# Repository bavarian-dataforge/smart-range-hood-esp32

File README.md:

# Smart Range Hood ESP32

**English** · [Deutsch](README.de.md)

**Open-source ESP32 controller for a GUTMANN kitchen range hood**

An open-source project to replace the unavailable original control electronics of a GUTMANN kitchen extractor hood with a custom ESP32-based controller.

The project combines embedded firmware, PCB design with KiCad, local operation and optional smart-home integration via MQTT and Home Assistant.

## Project Goals

- Replace the original range hood control board
- Control fan operation and lighting
- Provide multiple fan speed levels and a boost mode
- Support local operation without Wi-Fi
- Integrate with Home Assistant via MQTT
- Develop a documented, maintainable hardware and software solution

## Existing Hardware

| Component | Specification |
|---|---|
| Range hood | GUTMANN |
| Motor | 109942-00 |
| Supply | 230 V AC / 50 Hz |
| Rated power | 260 W |
| Rated current | 1.15 A |
| Rated speed | 2100 rpm |
| Run capacitor | 6.5 µF / 450 V AC |
| Available PCB space | 140 × 180 mm |
| EMI filter | Schurter FMW2-52-6/0.5 (5500.2044), 6 A — kept in the supply line |
| Lighting | 12 V G4 spots (to be replaced by G4 LED) |
| Controller | ESP32-WROOM-32U DevKitC V4 |

The motor has been successfully tested at full speed.

The motor is a single-phase permanent-split capacitor (PSC) motor: main winding, auxiliary winding with a 6.5 µF run capacitor, thermal cut-out. It has no speed taps.

## Speed Control

**Capacitive step speed control** (no phase-angle control — PSC motors hum and overheat on triac dimmers):

| Level | Relay | Series capacitor | Note |
|---|---|---|---|
| 3 (full) | K1 | none, direct | identical to the motor on mains |
| 2 | K4 | ~15–20 µF / 450 V AC | estimate, tune in bench test |
| 1 | K3 | ~10–12 µF / 450 V AC | estimate, tune in bench test |
| (reserve) | K2 | — | optional 4th level |

A series capacitor acts as a nearly loss-free reactance (X = 1/(2πfC)) and lowers the motor voltage. Relays are interlocked in firmware; every start from standstill runs 2 s at full speed (kick-start) before dropping to the target level.

Estimate: motor ≈ 200 Ω (230 V / 1.15 A, nearly resistive with its run capacitor); motor voltage = 230 V · R / √(R² + X_C²). The values are validated on the bench before the PCB is ordered — see [test setup](docs/images/testaufbau-kondensatoren.png).

## Planned Architecture

```text
Local User Interface
         |
         v
       ESP32 <---- Wi-Fi / MQTT
         |              |
         |        Home Assistant
         |
         v
ULN2003A relay driver          AO3400A MOSFET
         |                            |
   4 relays (Finder 40.31)      12 V LED lighting (PWM dimming)
         |
   series capacitors  ---->  Fan motor (PSC, 230 V)

Mains: fuse T 2.5 A, varistor, X2 capacitor, Mean Well IRM-20-12 (isolated 12 V)
Fallback control: Shelly BLU button (BLE, works without Wi-Fi)
```

## Repository Structure

```text
smart-range-hood-esp32/
├── README.md                 # English
├── README.de.md              # German
├── docs/
│   ├── konzept.md            # full concept, checklists, test plan (German)
│   └── images/               # nameplates, filter, hood terminal space
├── hardware/
│   ├── kicad/                # Python generators + KiCad project
│   │   ├── generate_schematic.py
│   │   ├── generate_pcb.py   # placement, net classes, design rules
│   │   ├── route_pcb.py      # own router (8 mm mains/SELV, 3 mm mains/mains)
│   │   ├── make_3d_terminals.py
│   │   └── dunstabzug-steuerplatine/
│   ├── gerber/               # fabrication output
│   ├── traegerplatte/        # carrier plate drilling template 1:1 (Python → SVG)
│   └── einkaufsliste-reichelt.md   # BOM with Reichelt links (German)
└── firmware/
    └── esphome/              # ESPHome test configurations
```

## Development Roadmap

- [x] Identify motor specifications
- [x] Verify motor operation at full speed
- [x] Confirm suitable motor speed-control method
- [x] Identify lighting supply and control requirements
- [x] Define ESP32 hardware architecture
- [x] Create KiCad schematic
- [x] Design PCB (160 × 100 mm, 2 layers, THT, DRC clean)
- [ ] Bench-test series capacitor values
- [ ] Electrical review of the mains side, then order PCB
- [ ] Implement ESP32 firmware (ESPHome test configs exist)
- [ ] Integrate MQTT and Home Assistant
- [ ] Perform electrical safety and functional testing

## Build the PCB from source

```bash
KP=/Applications/KiCad/KiCad.app/Contents/Frameworks/Python.framework/Versions/3.9/bin/python3   # KiCad's Python (macOS)
cd hardware/kicad
$KP generate_schematic.py
$KP generate_pcb.py && python3 route_pcb.py && $KP generate_pcb.py --apply-routes
```

## Electrical Safety

This project involves **230 V AC mains voltage** and a motor with a run capacitor.

The ESP32 low-voltage circuitry must be galvanically isolated from hazardous mains circuits. Appropriate protection, creepage and clearance distances, thermal design, enclosure requirements and EMC considerations must be addressed.

Motor control must not be implemented using an unverified dimmer or PWM circuit. Any mains-powered hardware requires appropriate professional review and testing before operation.

## Project Status

**PCB designed, awaiting electrical review and bench test.**

Schematic (ERC clean), routed PCB (DRC clean, 8 mm clearance/creepage mains ↔ SELV with milled slot, 3 mm mains ↔ mains) and Gerber files exist. Not yet built or tested — do not use as-is.

## License

To be determined.

---

Developed by **Bavarian Data Forge**.

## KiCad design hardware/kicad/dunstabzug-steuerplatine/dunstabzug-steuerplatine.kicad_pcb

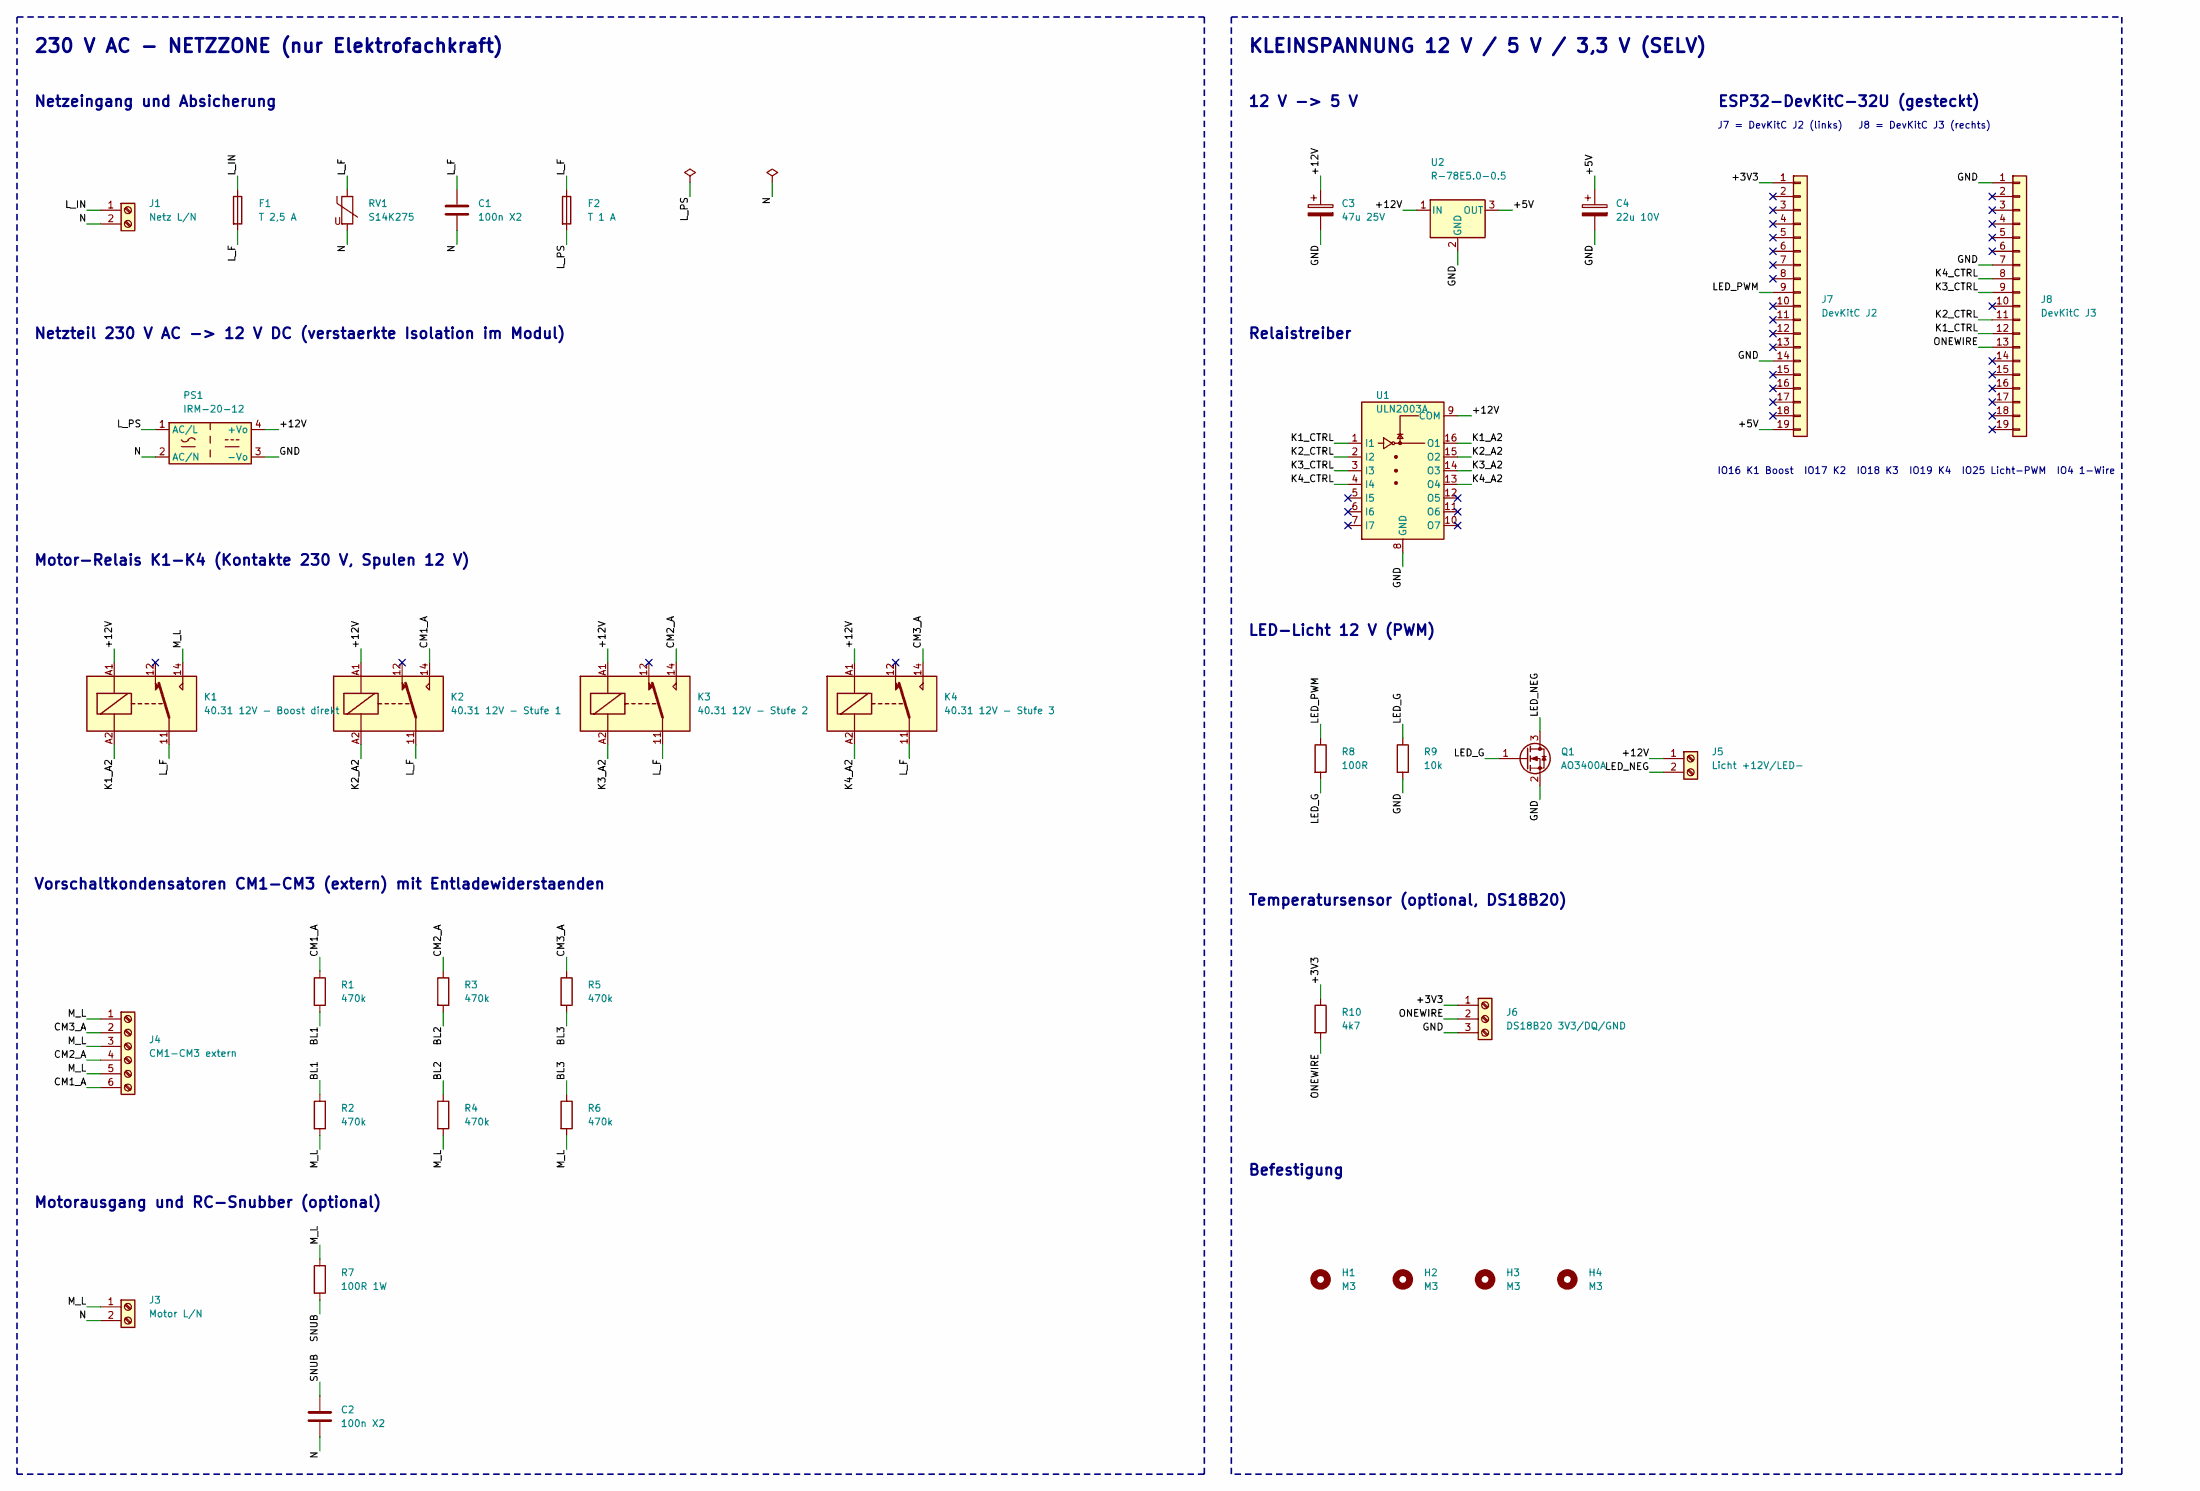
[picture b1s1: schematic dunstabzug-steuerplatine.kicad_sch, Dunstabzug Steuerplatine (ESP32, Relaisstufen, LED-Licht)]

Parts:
C1, C2: 100n X2; C_Rect_L18.0mm_W6.0mm_P15.00mm_FKS3_FKP3
C3: 47u 25V; CP_Radial_D6.3mm_P2.50mm
C4: 22u 10V; CP_Radial_D6.3mm_P2.50mm
F1: T 2,5 A; Fuseholder_Cylinder-5x20mm_Schurter_0031_8201_Horizontal_Op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
F2: T 1 A; Fuseholder_Cylinder-5x20mm_Schurter_0031_8201_Horizontal_Op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
H1, H2, H3, H4: M3; MountingHole_3.2mm_M3
J1: Netz L/N; TerminalBlock_MetzConnect_Type171_RT13702HBWC_1x02_P7.50mm_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
J3: Motor L/N; TerminalBlock_MetzConnect_Type171_RT13702HBWC_1x02_P7.50mm_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
J4: CM1-CM3 extern; TerminalBlock_MetzConnect_Type171_RT13706HBWC_1x06_P7.50mm_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
J5: Licht +12V/LED-; TerminalBlock_Phoenix_MKDS-1,5-2-5.08_1x02_P5.08mm_Horizont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
J6: DS18B20 3V3/DQ/GND; TerminalBlock_Phoenix_MKDS-1,5-3-5.08_1x03_P5.08mm_Horizont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
J7: DevKitC J2; PinSocket_1x19_P2.54mm_Vertical
J8: DevKitC J3; PinSocket_1x19_P2.54mm_Vertical
K1: 40.31 12V - Boost direkt; Relay_SPDT_Finder_40.31
K2: 40.31 12V - Stufe 1; Relay_SPDT_Finder_40.31
K3: 40.31 12V - Stufe 2; Relay_SPDT_Finder_40.31
K4: 40.31 12V - Stufe 3; Relay_SPDT_Finder_40.31
PS1: IRM-20-12; Converter_ACDC_MeanWell_IRM-20-xx_THT
Q1: AO3400A; SOT-23
R1, R2, R3, R4, R5, R6: 470k; R_Axial_DIN0207_L6.3mm_D2.5mm_P10.16mm_Horizontal
R7: 100R 1W; R_Axial_DIN0414_L11.9mm_D4.5mm_P15.24mm_Horizontal
R8: 100R; R_Axial_DIN0207_L6.3mm_D2.5mm_P10.16mm_Horizontal
R9: 10k; R_Axial_DIN0207_L6.3mm_D2.5mm_P10.16mm_Horizontal
R10: 4k7; R_Axial_DIN0207_L6.3mm_D2.5mm_P10.16mm_Horizontal
RV1: S14K275; RV_Disc_D15.5mm_W4.3mm_P7.5mm
U1: ULN2003A; DIP-16_W7.62mm
U2: R-78E5.0-0.5; Converter_DCDC_RECOM_R-78E-0.5_THT

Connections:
/+3V3: J6.1, J7.1, R10.1
/+5V: C4.1, J7.19, U2.3 (OUT)
/+12V: C3.1, J5.1, K1.A1, K2.A1, K3.A1, K4.A1, PS1.4 (+Vo), U1.9 (COM), U2.1 (IN)
/BL1: R1.2, R2.1
/BL2: R3.2, R4.1
/BL3: R5.2, R6.1
/CM1_A: J4.6, K2.14, R1.1
/CM2_A: J4.4, K3.14, R3.1
/CM3_A: J4.2, K4.14, R5.1
/GND: C3.2, C4.2, J6.3, J7.14, J8.1, J8.7, PS1.3 (-Vo), Q1.2 (S), R9.2, U1.8 (GND), U2.2 (GND)
/K1_A2: K1.A2, U1.16 (O1)
/K1_CTRL: J8.12, U1.1 (I1)
/K2_A2: K2.A2, U1.15 (O2)
/K2_CTRL: J8.11, U1.2 (I2)
/K3_A2: K3.A2, U1.14 (O3)
/K3_CTRL: J8.9, U1.3 (I3)
/K4_A2: K4.A2, U1.13 (O4)
/K4_CTRL: J8.8, U1.4 (I4)
/LED_G: Q1.1 (G), R8.2, R9.1
/LED_NEG: J5.2, Q1.3 (D)
/LED_PWM: J7.9, R8.1
/L_F: C1.1, F1.2, F2.1, K1.11, K2.11, K3.11, K4.11, RV1.1
/L_IN: F1.1, J1.1
/L_PS: F2.2, PS1.1 (AC/L)
/M_L: J3.1, J4.1, J4.3, J4.5, K1.14, R2.2, R4.2, R6.2, R7.1
/N: C1.2, C2.2, J1.2, J3.2, PS1.2 (AC/N), RV1.2
/ONEWIRE: J6.2, J8.13, R10.2
/SNUB: C2.1, R7.2

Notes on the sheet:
230 V AC - NETZZONE (nur Elektrofachkraft)
Netzeingang und Absicherung
Netzteil 230 V AC -> 12 V DC (verstaerkte Isolation im Modul)
Motor-Relais K1-K4 (Kontakte 230 V, Spulen 12 V)
Vorschaltkondensatoren CM1-CM3 (extern) mit Entladewiderstaenden
Motorausgang und RC-Snubber (optional)
KLEINSPANNUNG 12 V / 5 V / 3,3 V (SELV)
12 V -> 5 V
Relaistreiber
ESP32-DevKitC-32U (gesteckt)
J7 = DevKitC J2 (links) J8 = DevKitC J3 (rechts)
IO16 K1 Boost IO17 K2 IO18 K3 IO19 K4 IO25 Licht-PWM IO4 1-Wire
LED-Licht 12 V (PWM)
Temperatursensor (optional, DS18B20)
Befestigung

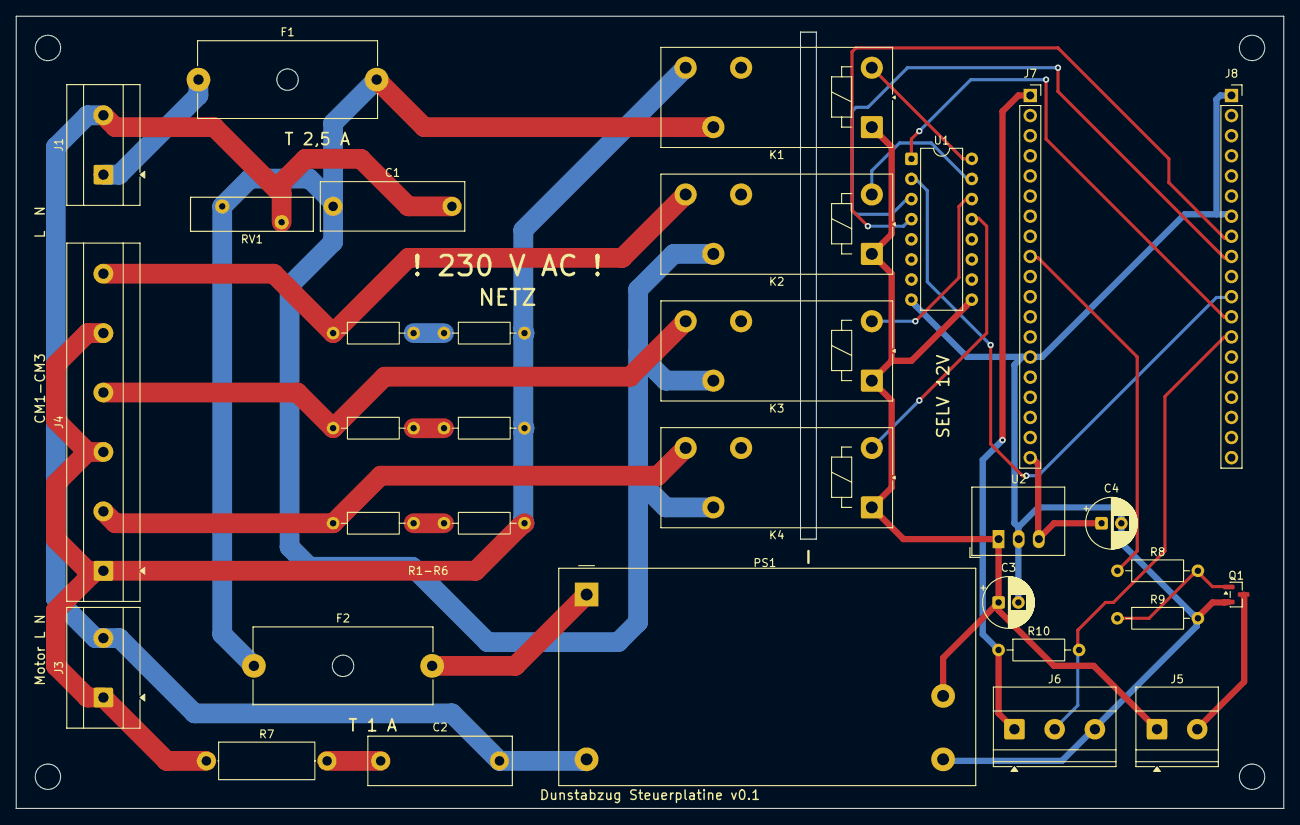
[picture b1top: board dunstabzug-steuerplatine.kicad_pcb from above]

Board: 2 copper layers, 160.0 x 100.0 mm, 36 parts (0 on the bottom side), 28 nets.
